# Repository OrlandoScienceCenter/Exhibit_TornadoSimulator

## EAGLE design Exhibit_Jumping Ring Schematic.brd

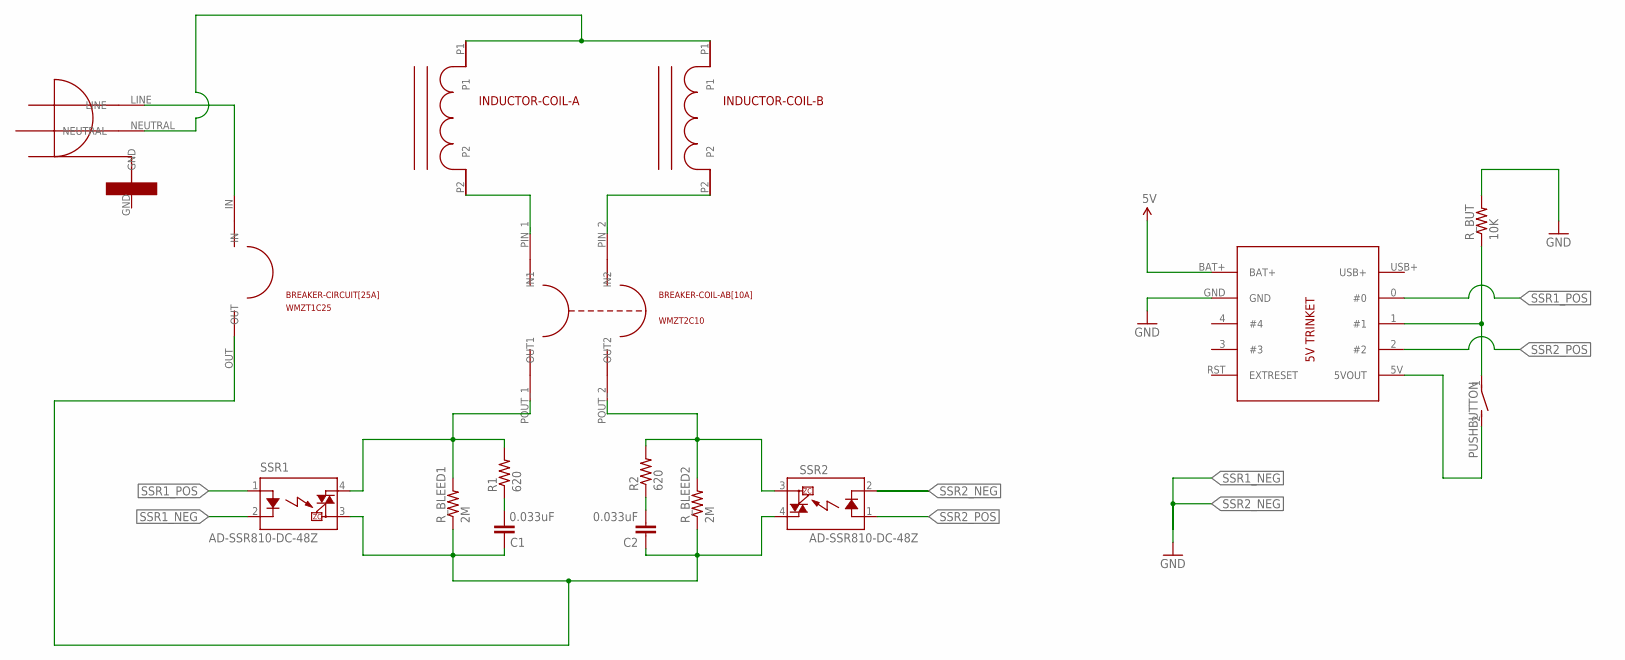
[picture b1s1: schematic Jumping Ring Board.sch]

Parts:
BREAKER-CIRCUIT[25A]: WMZT1C25; WMZT-1P
BREAKER-COIL-AB[10A]: WMZT2C10; WMZT-2P
C1, C2: 0.033uF; C5B2.5
INDUCTOR-COIL-A: IRON-CORE-INDUCTOR-COIL; INDUCTOR-PADS
INDUCTOR-COIL-B: IRON-CORE-INDUCTOR-COIL; INDUCTOR-PADS
PUSHBUTTON: DS01E; DS-01
R1, R2: 620; 0204/7
R_BLEED1, R_BLEED2: 2M; 0204/7
R_BUT: 10K; 0204/7
SSR1, SSR2: AD-SSR810-DC-48Z; SOP04
U$1: TRINKET5V
U$2: AC-SOURCE

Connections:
5V: U$1.BAT+
GND: R_BUT.2, U$1.GND
unnamed: PUSHBUTTON.1, R_BUT.1, U$1.1 (#1)
unnamed: BREAKER-CIRCUIT[25A].IN, U$2.LINE
unnamed: C1.1, C2.1, R_BLEED1.1, R_BLEED2.1, SSR1.3 (DS2), SSR2.4 (DS1)
unnamed: BREAKER-COIL-AB[10A].PIN_1 (IN1), INDUCTOR-COIL-A.P2
unnamed: BREAKER-COIL-AB[10A].PIN_2 (IN2), INDUCTOR-COIL-B.P2
unnamed: C1.2, R1.1
unnamed: BREAKER-COIL-AB[10A].POUT_2 (OUT2), R2.2, R_BLEED2.2, SSR2.3 (DS2)
unnamed: PUSHBUTTON.2, U$1.5V (5VOUT)
unnamed: BREAKER-COIL-AB[10A].POUT_1 (OUT1), R1.2, R_BLEED1.2, SSR1.4 (DS1)
unnamed: C2.2, R2.1
unnamed: INDUCTOR-COIL-A.P1, INDUCTOR-COIL-B.P1, U$2.NEUTRAL
SSR1_NEG: SSR1.2 (K)
SSR1_POS: SSR1.1 (A), U$1.0 (#0)
SSR2_NEG: SSR2.2 (K)
SSR2_POS: SSR2.1 (A), U$1.2 (#2)

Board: 2 copper layers, 16 parts (0 on the bottom side), 14 nets, no tracks yet.

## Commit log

2015-07-05 Added Jumping Ring Sketch
    Added Jumping Ring Sketch
2015-07-06 Added comments, integers for certain values
2015-07-06 Added Jumping Ring Schematic
2015-07-06 Renamed Files
2015-07-06 Added BOM
2016-04-25 Added files via upload

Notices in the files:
parts and their libraries:
SparkFun-Aesthetics: Licensing: Creative Commons ShareAlike 4.0 International - https://creativecommons.org/licenses/by-sa/4.0
